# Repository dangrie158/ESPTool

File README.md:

# ESPTool
## A WiFi Security Swiss Army Knife

The ESPTool is a convenient Tool to test your WiFi Security against attackers.
It can demonstrate how easy it is to crack a WiFi Password or jam your WiFi so you cant access the internet.
This Tool is designed for education and self tests.

**Be aware that it is illegal to use this device on Networks other than your own.**

_**Disclaimer** The authors of this reposity are not accountable for any action users may perform with this tool_

## Hardware

The Hardware is designed to be a relative generic and reusable Module around the ESP8266 WiFi Plattform. The Schematic is loosley based on the [NodeMCU](http://nodemcu.com) Project, however instead of breaking out all the free pins, all pins are used for a bunch of devices.

The Device has the following Hardware

* SSD1306 based OLED Display, connected via I2C
* microSD Card Socket connected over the SPI interface
* 3 general purpose buttons
* ESP8266-12E Module
* TPS63031 Buck-/Boost-Converter with an input range from 1.8V - 5.5V
* MCP73831 Single-Cell LiPo Charger Chip
* CP2012 USB to UART converter Chip

## Software
The software is of course the part where all the security features are implemented.

It still is under heavy development. A List of planned features are listed here:

* Layer 1:
	* *Since the ESPs Radio is not really configurable it is not possible to create a WiFi Jammer that works by emitting broadband noise or any other Layer 1 attacks*
* Layer 2:
	* [Deauthentification attack](https://en.wikipedia.org/wiki/Wi-Fi_deauthentication_attack)
	* collecting authentification frames and save the keys to SD card for later decryption (using a wordlist on a computer, the ESP neither has enough memory nor enough processing power to crack them on the system)
	* arp spoofing and session hijacking when connected (needs investigation)
* Layer 3 (after connecting to an AP):
	* Host discovery (IP Scanner)
	* Ping flooding (ICMP Pings)
* Layer 4 (after connecting to an AP):
	* Port Scan on Host

### Incognito Features (TBD):
* Random MAC-Address on Power Up
* Random Mac Address while performing critical Tasks

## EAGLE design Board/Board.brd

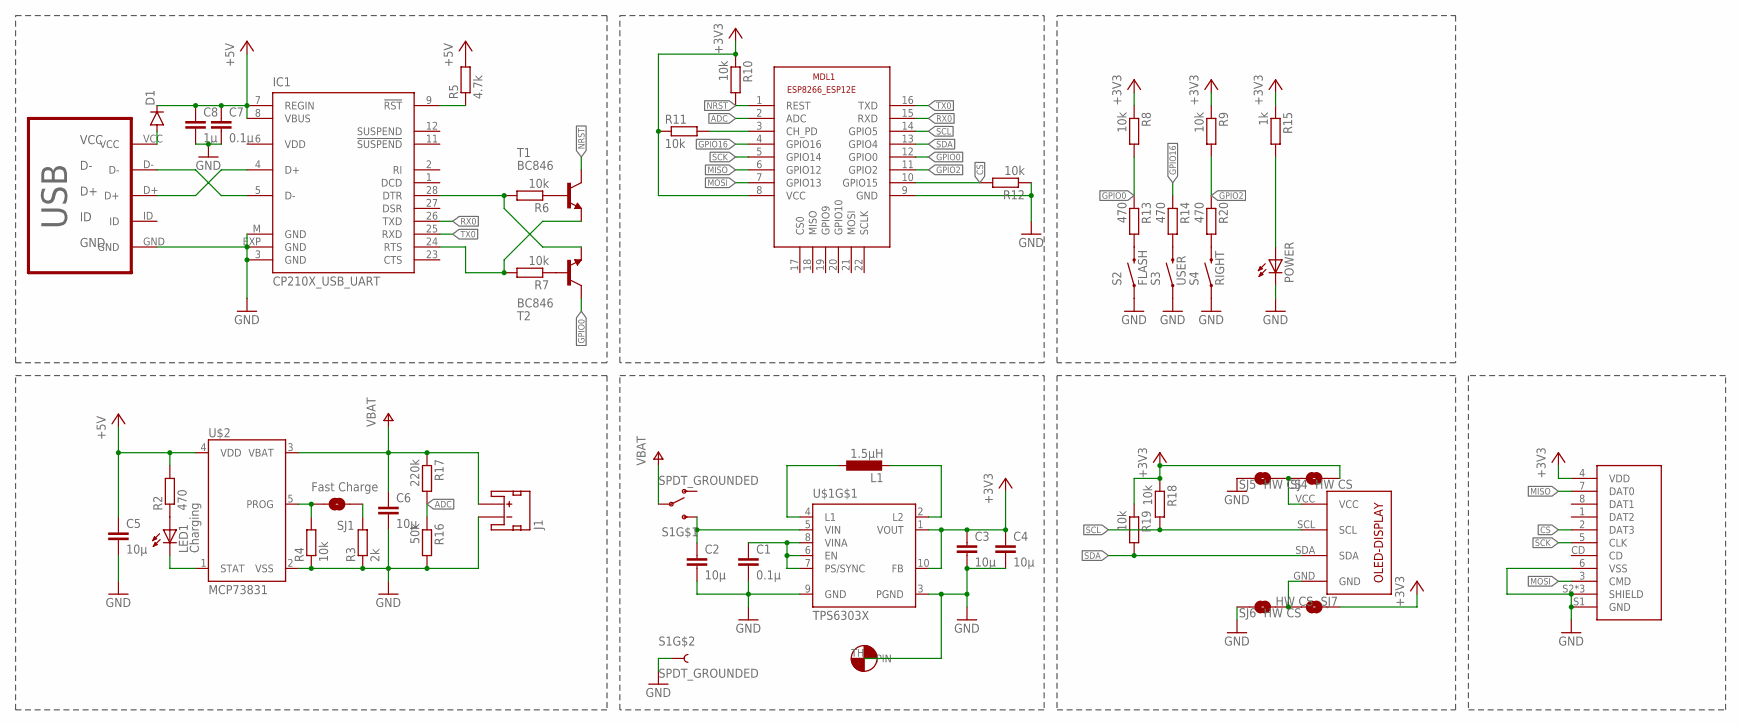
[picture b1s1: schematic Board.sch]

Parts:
C1, C7: 0.1µ; C0603
C2, C3, C4, C5, C6: 10µ; C0603
C8: 1µ; C0603
D1: DIODEBAS16; SOD-323
IC1: CP210X_USB_UART; MLP28
J1: JST_2MM_MALE; JST-2-SMD
L1: 1.5µH; L3225P
LED1: Charging; SML0805
MDL1: ESP8266-12EESP8266-ESP12E; ESP8266-ESP12E
POWER: LEDSML0805; SML0805
R2, R13, R14, R20: 470; R0603
R3: 2k; R0603
R4, R6, R7, R8, R9, R10, R11, R12, R18, R19: 10k; R0603
R5: 4.7k; R0603
R15: 1k; R0603
R16: 50k; R0603
R17: 220k; R0603
S1: SPDT_GROUNDED; SWITCH-SPST-SMD-A
S2: FLASH; TACTILE-SWITCH-1101NE
S3: USER; TACTILE-SWITCH-1101NE
S4: RIGHT; TACTILE-SWITCH-1101NE
SJ1: Fast Charge; SJ_2S-NO
SJ4, SJ5, SJ6, SJ7: HW CS; SJ_2S-NO
T1, T2: BC846; SOT23
U$1: TPS6303X; DSK10
U$2: MCP73831; SOT23-5
U$3: MICRO-USB-B; MICRO_USB_4_LEGS
U$4: MICRO_SD_SOCKET; MICRO_SD
U$6: OLED-I2C

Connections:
+3V3: C3.1, C4.1, MDL1.8 (VCC), R8.1, R9.1, R10.1, R11.1, R15.1, R18.1, R19.1, SJ4.1, SJ7.2, U$1.1 (VOUT), U$1.10 (FB), U$4.4 (VDD)
+5V: C5.1, C7.1, C8.1, D1.C, IC1.7 (REGIN), IC1.8 (VBUS), R2.2, R5.2, U$2.4 (VDD)
ADC: MDL1.2 (ADC), R16.1, R17.2
CS: MDL1.10 (GPIO15), R12.2, U$4.2 (DAT3)
GND: C1.2, C2.2, C3.2, C4.2, C5.2, C6.2, C7.2, C8.2, IC1.3 (GND), IC1.EXP (GND), IC1.M (GND), J1.1 (-), MDL1.9 (GND), POWER.C, R3.1, R4.1, R12.1, R16.2, S1.GND1 (1), S1.GND2 (1), S1.GND3 (1), S1.GND4 (1), S2.1, S3.1, S4.1, SJ5.2, SJ6.2, U$1.3 (PGND), U$1.9 (GND), U$1.TH (PIN), U$2.2 (VSS), U$3.GND, U$4.6 (VSS), U$4.S1 (GND), U$4.S2 (SHIELD), U$4.S3 (SHIELD), U$4.S4 (SHIELD)
GPIO0: MDL1.12 (GPIO0), R8.2, R13.1, T2.3 (C)
GPIO2: MDL1.11 (GPIO2), R9.2, R20.1
GPIO16: MDL1.4 (GPIO16), R14.1
MISO: MDL1.6 (GPIO12), U$4.7 (DAT0)
MOSI: MDL1.7 (GPIO13), U$4.3 (CMD)
unnamed: L1.1, U$1.4 (L1)
unnamed: L1.2, U$1.2 (L2)
unnamed: IC1.9 (!RST), R5.1
unnamed: D1.A, U$3.VCC
unnamed: IC1.5 (D-), U$3.D-
unnamed: C1.1, U$1.6 (EN), U$1.7 (PS/SYNC), U$1.8 (VINA)
unnamed: LED1.A, R2.1
unnamed: R4.2, SJ1.1, U$2.5 (PROG)
unnamed: LED1.C, U$2.1 (STAT)
unnamed: R3.2, SJ1.2
unnamed: MDL1.3 (CH_PD), R11.2
unnamed: IC1.4 (D+), U$3.D+
unnamed: IC1.28 (DTR), R6.2, T2.2 (E)
unnamed: R7.1, T2.1 (B)
unnamed: C2.1, S1.3 (S), U$1.5 (VIN)
unnamed: R6.1, T1.1 (B)
unnamed: IC1.24 (RTS), R7.2, T1.2 (E)
unnamed: R14.2, S3.2
unnamed: R13.2, S2.2
unnamed: POWER.A, R15.2
unnamed: SJ4.2, SJ5.1, U$6.VCC
unnamed: SJ6.1, SJ7.1, U$6.GND
unnamed: R20.2, S4.2
NRST: MDL1.1 (REST), R10.2, T1.3 (C)
RX0: IC1.26 (TXD), MDL1.15 (RXD)
SCK: MDL1.5 (GPIO14), U$4.5 (CLK)
SCL: MDL1.14 (GPIO5), R18.2, U$6.SCL
SDA: MDL1.13 (GPIO4), R19.2, U$6.SDA
TX0: IC1.25 (RXD), MDL1.16 (TXD)
V+: C6.1, J1.2 (+), R17.1, S1.2, U$2.3 (VBAT)
VDD: IC1.6 (VDD)

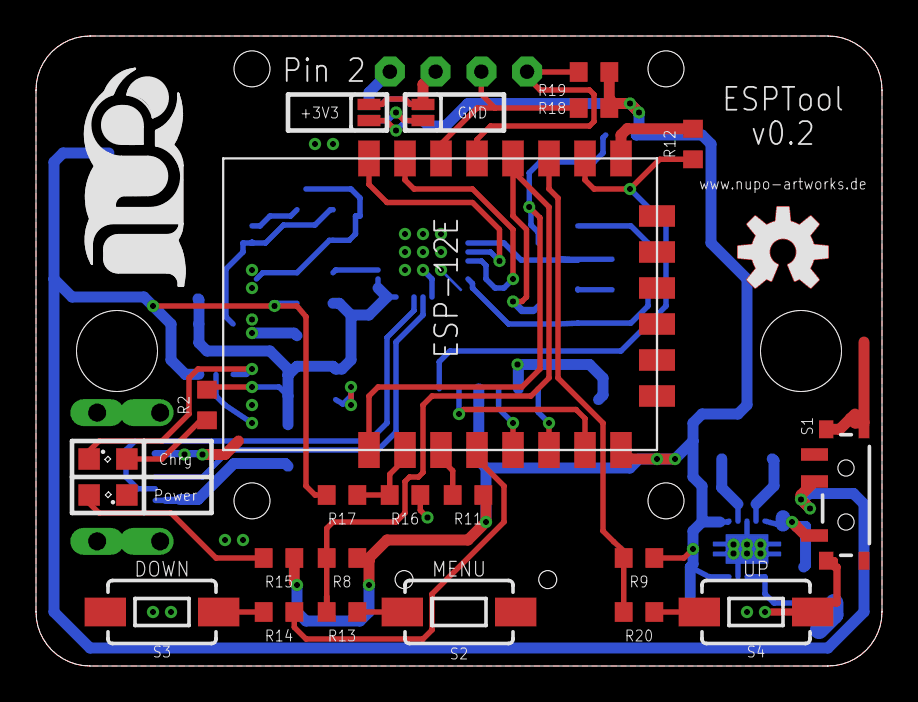
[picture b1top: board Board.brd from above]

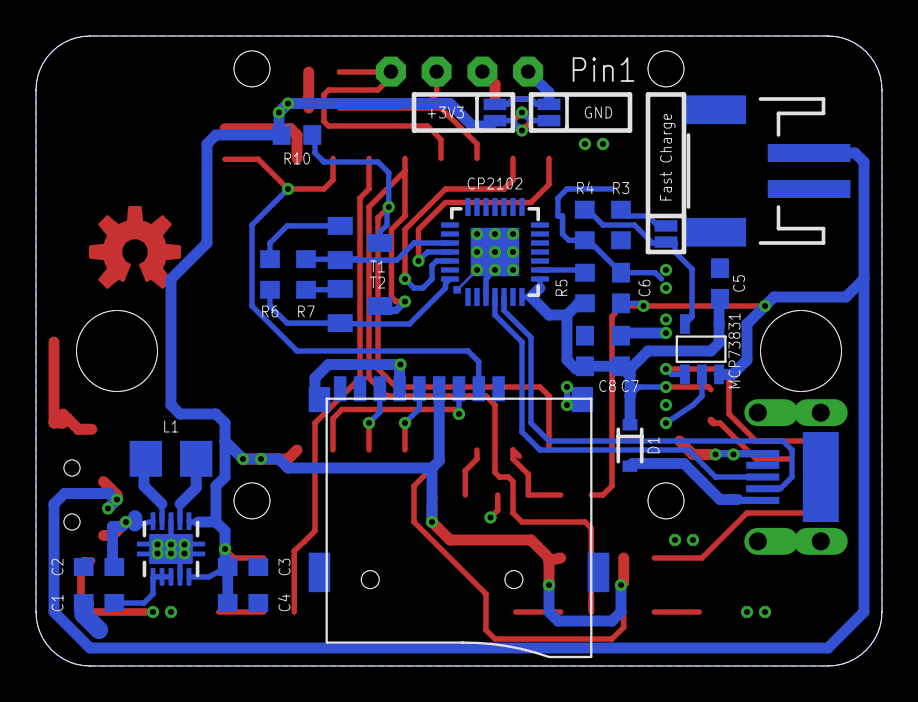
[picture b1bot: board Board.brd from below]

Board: 2 copper layers, 47.0 x 35.0 mm, 53 parts (27 on the bottom side), 40 nets.

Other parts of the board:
U$5: LOGO-SILKSCREEN
U$7: OSHW-LOGO-M
U$8: OSHW-LOGO-M_COPPER

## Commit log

2016-06-28 added gitignore
2016-06-29 placed silkscreen
2016-06-29 added lables for navigation buttons
2016-06-29 added lables to user and flash button
2016-06-29 removed soldermask from vias
2016-07-25 cleanup schematic
2016-07-25 moved pins to new spi out and removed unused components
2016-07-26 cleanup
2016-07-27 added copper file
2016-07-27 restructured repo to add firmware
2016-07-27 added readme
2016-07-27 moved README to main directory
2016-07-27 added MIT Licence
2016-07-29 added reference designators to CS Line
2016-07-29 added .pioenvs generated files to gitignore
2016-07-29 added ScanProcess to Scan for APs
2016-07-29 Added Released Event after Button was held
2016-07-29 removed unnececary btn delay check
2016-07-29 added a Text Input Screen
2016-07-29 added callback to ScanProcess
2016-08-01 added opt-in double click functionality to buttons
2016-08-01 added switch to disable list items to be selectable in ListScreen
    this is handy if you want to display simple lists that are not selectable but scrollable (e.g. results or a summary)
2016-08-01 moved label on LoadingScreen closer to the top
    this now allows for a 2 lined label
2016-08-01 rearranged elements on TextInputScreen
2016-08-01 added ConnectScreen that allows the User to connect to a wifi and entera passphrase if needed
2016-08-03 Added first Version of Pinger
    Support for Ping flooding
    Support for sinle Pings
2016-08-03 added function to LinkedList to delete a node by data
2016-08-03 refactored scan process to make it reusable
2016-08-03 added BarGraphScreen
2016-08-03 added OccupationProcess to display WiFi channel occupation
2016-08-03 fixed ListScreen for scrolling with no selection
2016-08-03 implemented example for pinger
2016-08-04 added NULL initialization of LinkedList root
2016-08-04 Fixed Pinger when sending multiple Pings simultaneously
2016-08-05 added Credential Class to store WiFi Credentials on SPIFFS
2016-08-05 added CredentialCache to Connect Process to save passphrases between boots
2016-08-05 added ping response time to pinger and pinger callback
2016-08-05 added arbitrary callback argument to pinger setCallback
2016-08-05 added MessageScreen to show simple messages with one action button
2016-08-05 added method to preset the text of a TextInputScreen
2016-08-05 moved ScanProcess callback to Process to make it available to all Processes
2016-08-05 fixed passing wrong arg to Pinger callback
2016-08-16 added missing connection in rev2 on TX net
2016-08-16 added wifi connection status icon to statusbar
2016-08-16 removed extraneous serial output from credential cache
2016-08-16 added missing wifi icon
2016-08-16 fixed memory leaks caused by erroneous LinkedList implementation
2016-08-16 fixed pinger to provide a nice interface and accept the ip while sending, not in constructor
2016-08-16 fixed text alignment in MessageScreen
2016-08-16 added callback call to ConnectProcess
2016-08-16 added items() function to list screen that returns a pointer to the linked list holding the items
2016-08-16 added scan host process that scans a complete subnet for hosts
2016-08-16 added Scan Host Process as next process when connected to a WiFi
    this is still only testing code
2017-01-20 added pdf schematic

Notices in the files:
parts and their libraries:
GeekAmmo: Licensing:Creative Commons ShareAlike 4.0 International - https://creativecommons.org/licenses/by-sa/4.0
